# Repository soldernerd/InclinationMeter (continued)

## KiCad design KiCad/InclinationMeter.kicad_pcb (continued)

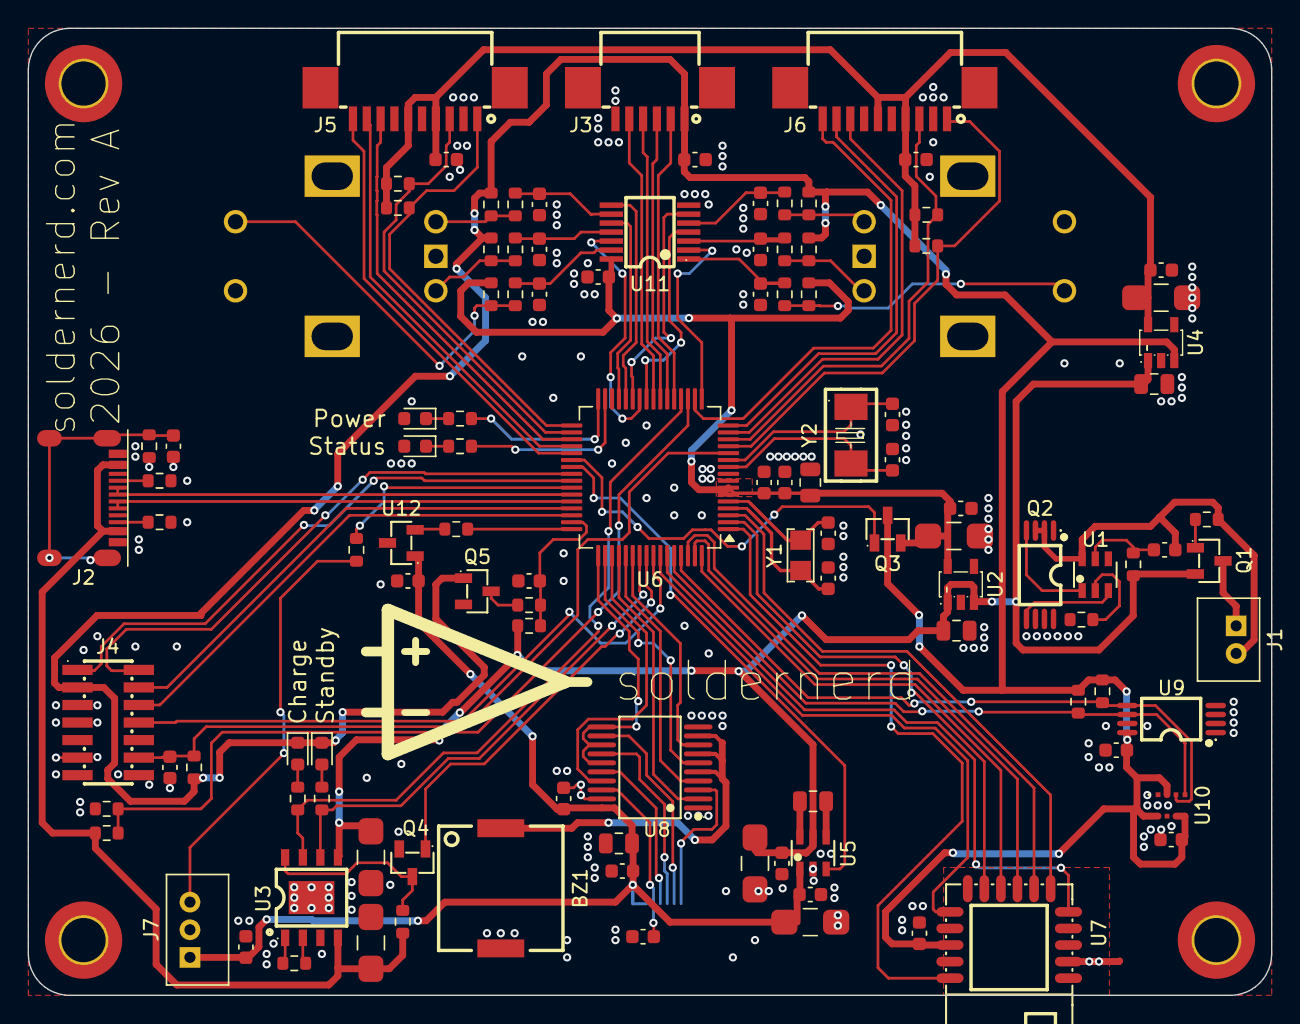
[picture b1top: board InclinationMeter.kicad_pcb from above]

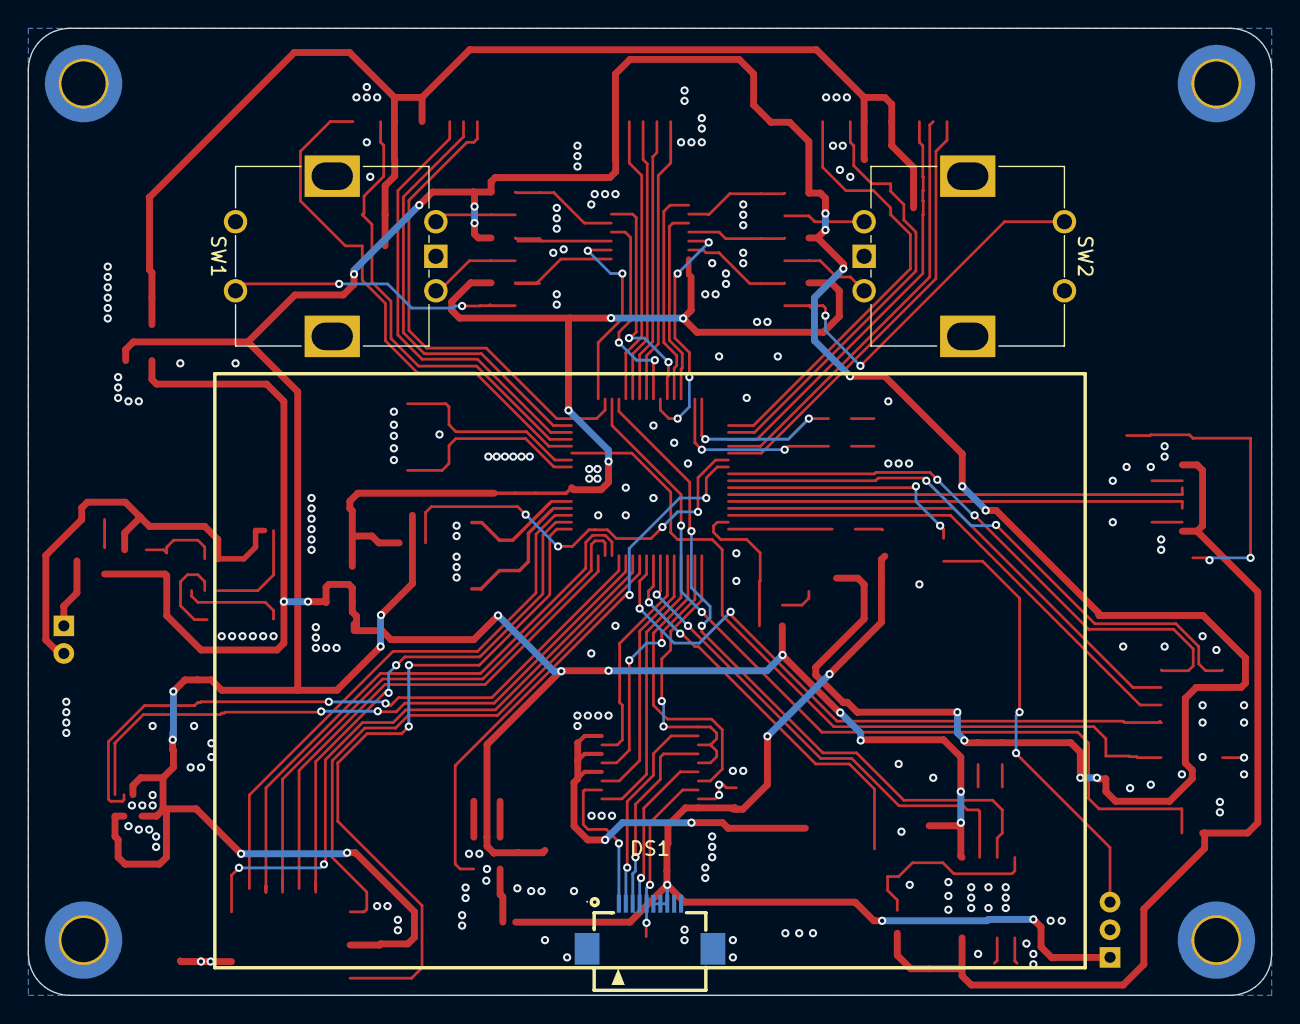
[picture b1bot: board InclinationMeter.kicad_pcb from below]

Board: 4 copper layers, 90.0 x 70.0 mm, 118 parts (3 on the bottom side), 105 nets.

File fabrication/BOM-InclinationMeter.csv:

"Comment","Designator","Footprint","LCSC Part #"
"CPT-9019A-SMT-TR","BZ1","sldrnrd:CPT-9019A","C20181991"
"1u","C1,C6,C16","sldrnrd:C_0805","C28323"
"100n","C2,C3,C8,C11,C12,C13,C17,C18,C23,C26,C27,C28,C30,C32,C34,C35,C36,C37,C38,C39,C40,C41,C42,C43","sldrnrd:C_0603","C14663"
"10u","C4,C5,C7,C9,C10,C14","sldrnrd:C_1206","C70462"
"2u2","C15,C29","sldrnrd:C_0805","C126589"
"15p","C19,C20","sldrnrd:C_0603","C1644"
"33p","C21,C22","sldrnrd:C_0603","C1663"
"10n","C24,C25,C31,C33","sldrnrd:C_0603","C57112"
"LED_Red_0603","D1","sldrnrd:LED_0603","C2286"
"LED_Green_0603","D2,D3","sldrnrd:LED_0603","C72043"
"LED_Yellow_0603","D4","sldrnrd:LED_0603","C2287"
"LS027B7DH01","DS1","sldrnrd:Display_LS027B7DH01","C17492463"
"JST_PH_2.0mm_1x02","J1","sldrnrd:JST_PH_2.0mm_1x02","C131337"
"USB_C","J2","sldrnrd:USB_C","C165948"
"Header_FFC_1.0mm_06","J3","sldrnrd:Header_FFC_1.0mm_06","C72727"
"Header_50mil_2x07","J4","sldrnrd:Header_50mil_2x07","C5563894"
"Header_FFC_1.0mm_10","J5,J6","sldrnrd:Header_FFC_1.0mm_10","C52162"
"JST_PH_2.0mm_1x03","J7","sldrnrd:JST_PH_2.0mm_1x03","C131339"
"DMG2305UX-13","Q1,Q3","sldrnrd:SOT-23-3","C144153"
"FS8205A","Q2","sldrnrd:TSSOP-8","C14212"
"AO3400A","Q4,Q5","sldrnrd:SOT-23-3","C20917"
"100k","R1,R8,R28,R31","sldrnrd:R_0603","C25803"
"2k","R2,R26,R37","sldrnrd:R_0603","C22975"
"1k","R3,R6,R7,R10,R11","sldrnrd:R_0603","C21190"
"R_0603","R4","sldrnrd:R_0603",""
"33k","R5,R9,R12,R13,R14,R15,R16,R17,R20,R21,R22,R23,R24,R25,R34","sldrnrd:R_0603","C4216"
"5k1","R18,R19,R27,R29,R32,R33,R35,R36","sldrnrd:R_0603","C23186"
"68k","R30","sldrnrd:R_0603","C23231"
"PEC11R-4215F-S0024","SW1,SW2","sldrnrd:RotaryEncoder_PEC11R","C143790"
"DW01A","U1","sldrnrd:SOT-23-6","C85680"
"LP5907MFX-3.3/NOPB","U2,U4","sldrnrd:SOT-23-5","C80670"
"TP4056","U3","sldrnrd:ESOP-8","C382139"
"SD6210A","U5","sldrnrd:SOT-23-6","C250809"
"STM32G0B1RET6","U6","sldrnrd:LQFP-64","C2829307"
"RN4871-I/RM128","U7","sldrnrd:RN4871","C633941"
"SN74AHCT244DBR","U8","sldrnrd:SSOP-20","C2868870"
"24LC256-I/ST","U9","sldrnrd:TSSOP-8","C87823"
"BME280","U10","sldrnrd:LGA-8_2.5x2.5mm_P0.65mm","C92489"
"SN74HC14PWR","U11","sldrnrd:TSSOP-14","C6821"
"LM35","U12","sldrnrd:SOT-23-3","C9900081740"
"Q13FC1350000400","Y1","sldrnrd:CRYSTAL-3215","C32346"
"X50328MSB2GI","Y2","sldrnrd:CRYSTAL-3225","C115962"

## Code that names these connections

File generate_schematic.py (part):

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    # (name, pin_number, electrical_type)
    # Left side: pins 1–16 (top to bottom)
    left_pins = [
        ("PC11",    "1",  "bidirectional"),
        ("PC12",    "2",  "bidirectional"),
        ("PC13",    "3",  "bidirectional"),
        ("PC14",    "4",  "bidirectional"),
        ("PC15",    "5",  "bidirectional"),
        ("VBAT",    "6",  "power_in"),
        ("VREF+",   "7",  "power_in"),
        ("VDD",     "8",  "power_in"),
        ("VSS",     "9",  "power_in"),
        ("PF0",     "10", "input"),
        ("PF1",     "11", "output"),
        ("~{NRST}", "12", "input"),
        ("PC0",     "13", "bidirectional"),
        ("PC1",     "14", "bidirectional"),
        ("PC2",     "15", "bidirectional"),
        ("PC3",     "16", "bidirectional"),
    ]
    # Bottom side: pins 17–32 (left to right)
    bot_pins = [
        ("PA0",     "17", "bidirectional"),
        ("PA1",     "18", "bidirectional"),
        ("PA2",     "19", "bidirectional"),
        ("PA3",     "20", "bidirectional"),
        ("PA4",     "21", "bidirectional"),
        ("PA5",     "22", "bidirectional"),
        ("PA6",     "23", "bidirectional"),
        ("PA7",     "24", "bidirectional"),
        ("PC4",     "25", "bidirectional"),
        ("PC5",     "26", "bidirectional"),
        ("PB0",     "27", "bidirectional"),
        ("PB1",     "28", "bidirectional"),
        ("PB2",     "29", "bidirectional"),
        ("PB10",    "30", "bidirectional"),
        ("PB11",    "31", "bidirectional"),
        ("PB12",    "32", "bidirectional"),
    ]
    # Right side: pins 33–48 (bottom to top)
    right_pins = [
        ("PB13",    "33", "bidirectional"),
        ("PB14",    "34", "bidirectional"),
        ("PB15",    "35", "bidirectional"),
        ("PA8",     "36", "bidirectional"),
        ("PA9",     "37", "bidirectional"),
        ("PC6",     "38", "bidirectional"),
        ("PC7",     "39", "bidirectional"),
        ("PD8",     "40", "bidirectional"),
        ("PD9",     "41", "bidirectional"),
        ("PA10",    "42", "bidirectional"),
        ("PA11",    "43", "bidirectional"),
        ("PA12",    "44", "bidirectional"),
        ("PA13",    "45", "bidirectional"),
        ("PA14",    "46", "input"),
        ("PA15",    "47", "bidirectional"),
        ("PC8",     "48", "bidirectional"),
    ]
    # Top side: pins 49–64 (right to left)
    top_pins = [
        ("PC9",     "49", "bidirectional"),
        ("PD0",     "50", "bidirectional"),
        ("PD1",     "51", "bidirectional"),
        ("PD2",     "52", "bidirectional"),
        ("PD3",     "53", "bidirectional"),
        ("PD4",     "54", "bidirectional"),
        ("PD5",     "55", "bidirectional"),
        ("PD6",     "56", "bidirectional"),
        ("PB3",     "57", "bidirectional"),
        ("PB4",     "58", "bidirectional"),
        ("PB5",     "59", "bidirectional"),
        ("PB6",     "60", "bidirectional"),
        ("PB7",     "61", "bidirectional"),
        ("PB8",     "62", "bidirectional"),
        ("PB9",     "63", "bidirectional"),
        ("PC10",    "64", "bidirectional"),
    ]

    # Geometry: 16 pins per side, 2.54 mm spacing
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    # Pin connections per Netlist.md
    # Left side (pins 1-10): inputs from MCU (3.3V signals)
    p1 = pin("SN74AHCT244", "1", ax, ay)   # 1OE -> GND
    p2 = pin("SN74AHCT244", "2", ax, ay)   # 1A1 <- DISP_SCK
    p4 = pin("SN74AHCT244", "4", ax, ay)   # 1A2 <- DISP_MOSI
    p6 = pin("SN74AHCT244", "6", ax, ay)   # 1A3 <- DISP_CS
    p8 = pin("SN74AHCT244", "8", ax, ay)   # 1A4 <- DISP_VCOM
    p10 = pin("SN74AHCT244", "10", ax, ay)  # GND

    gnd(el, p1[0], p1[1])   # 1OE always enabled
    gnd(el, p10[0], p10[1])  # GND pin

    glabel_left(el, p2[0], p2[1], "DISP_SCK", "input")
    glabel_left(el, p4[0], p4[1], "DISP_MOSI", "input")
    glabel_left(el, p6[0], p6[1], "DISP_CS", "input")
    glabel_left(el, p8[0], p8[1], "DISP_VCOM", "input")

    # Spare inputs (3, 5, 7) - tie unused to GND (pin 9 is 2OE, handled below)
    for pn in ["3", "5", "7"]:
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        gnd(el, pp[0], pp[1])

    # Right side (pins 11-20): outputs (5V signals)
    p11 = pin("SN74AHCT244", "11", ax, ay)  # 2A1 <- DISP_ON
    p18 = pin("SN74AHCT244", "18", ax, ay)  # 1Y1 -> DISP_SCK_5V
    p16 = pin("SN74AHCT244", "16", ax, ay)  # 1Y2 -> DISP_MOSI_5V
    p14 = pin("SN74AHCT244", "14", ax, ay)  # 1Y3 -> DISP_CS_5V
    p12 = pin("SN74AHCT244", "12", ax, ay)  # 1Y4 -> DISP_VCOM_5V
    p9_r = pin("SN74AHCT244", "9", ax, ay)  # 2Y1 -> DISP_ON_5V
    p19 = pin("SN74AHCT244", "19", ax, ay)  # 2OE -> GND
    p20 = pin("SN74AHCT244", "20", ax, ay)  # VCC -> +5V

    glabel_left(el, p11[0], p11[1], "DISP_ON", "input")

    pwr5v(el, p20[0], p20[1])
    gnd(el, p19[0], p19[1])  # 2OE always enabled

    label_right(el, p18[0], p18[1], "DISP_SCK_5V")
    label_right(el, p16[0], p16[1], "DISP_MOSI_5V")
    label_right(el, p14[0], p14[1], "DISP_CS_5V")
    label_right(el, p12[0], p12[1], "DISP_VCOM_5V")
    label_right(el, p9_r[0], p9_r[1], "DISP_ON_5V")

    # Spare outputs: pins 13, 15, 17 -> tie inputs to GND already done above
    for pn in ["13", "15", "17"]:
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
    # Display connector pinout per Netlist.md
    jp = lambda n: pin("FH12_10S", str(n), jx, jy)
    label_left(el, jp(1)[0], jp(1)[1], "DISP_SCK_5V")
    label_left(el, jp(2)[0], jp(2)[1], "DISP_MOSI_5V")
    label_left(el, jp(3)[0], jp(3)[1], "DISP_CS_5V")
    label_left(el, jp(4)[0], jp(4)[1], "DISP_VCOM_5V")
    label_left(el, jp(5)[0], jp(5)[1], "DISP_ON_5V")
    pwr5v(el, jp(6)[0], jp(6)[1])   # EXTMODE tied to +5V
    pwr5v(el, jp(7)[0], jp(7)[1])   # VDD
    gnd(el, jp(8)[0], jp(8)[1])     # VSS
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
    # Right pins
    el.append(sexp_no_connect(rp(9)[0], rp(9)[1]))    # P3_6
    glabel_right(el, rp(10)[0], rp(10)[1], "BLE_RST", "input")  # RST_N
    glabel_right(el, rp(11)[0], rp(11)[1], "BLE_STATUS", "output")  # P0_0 status
    el.append(sexp_no_connect(rp(12)[0], rp(12)[1]))  # P0_2
    gnd(el, rp(13)[0], rp(13)[1])                      # GND
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    el.append(sexp_text("22R series on D+/D-", 60, 102, 1.27))

    # VBUS sense
    el.append(sexp_global_label("VBUS_SENSE", 50, 115, 0, "output"))
    el.append(sexp_text("Optional VBUS detect", 60, 122, 1.27))

    # ── SWD Debug Header J3 ──
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    gnd(el, fp("03")[0], fp("03")[1])                            # Pin 3: GND
    glabel_right(el, fp("04")[0], fp("04")[1], "SWCLK", "output")       # Pin 4: SWCLK (via 100R)
    gnd(el, fp("05")[0], fp("05")[1])                            # Pin 5: GND
    el.append(sexp_no_connect(fp("06")[0], fp("06")[1]))        # Pin 6: SWO (NC)
    el.append(sexp_no_connect(fp("07")[0], fp("07")[1]))        # Pin 7: NC
    el.append(sexp_no_connect(fp("08")[0], fp("08")[1]))        # Pin 8: NC
    gnd(el, fp("09")[0], fp("09")[1])                            # Pin 9: GND
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    gnd(el, fp("14")[0], fp("14")[1])                            # Pin 14: GND

    el.append(sexp_text("100R series on SWDIO/SWCLK", 177, 120, 1.27))
    el.append(sexp_text("10k BOOT0 pull-down on PA14/SWCLK", 177, 127, 1.27))
    el.append(sexp_text("10k pull-up + 100nF on NRST", 177, 134, 1.27))

    # ── FFC Connectors (J5, J6, J7) ──
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    place_resistor(el, ld1x, ld1y, next_ref("R"), "330R")
    r1t = pin("R", "1", ld1x, ld1y)
    r1b = pin("R", "2", ld1x, ld1y)
    glabel_left(el, r1t[0], r1t[1], "LED_PWR", "input", 10)
    el.append(sexp_symbol_instance("inline:LED", next_ref("D"), "Green",
                                   "LED_SMD:LED_0603_1608Metric", ld1x, ld1y + 10))
    la = pin("LED", "1", ld1x, ld1y + 10)
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
    bp1 = pin("CPT_9019A", "1", bx, by)
    bp2 = pin("CPT_9019A", "2", bx, by)
    glabel_left(el, bp1[0], bp1[1], "BUZZER", "input")
    gnd(el, bp2[0], bp2[1])
    el.append(sexp_text("PWM 4kHz from TIM1_CH2 (PB3)", 217, 152, 1.27))

    # ── EEPROM ──
    el.append(sexp_rect(27, 170, 195, 270))
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    # Pin 3 (GND) → GND
    lm_gnd = pin("LM35", "3", lmx, lmy)
    gnd(el, lm_gnd[0], lm_gnd[1])
    # Pin 2 (VOUT) → R_TEMP 100R → C_TEMP 10nF → TEMP_SENSE global label
    lm_out = pin("LM35", "2", lmx, lmy)
    # Series resistor R_TEMP
    rt_ref = next_ref("R")
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    ct_ref = next_ref("C")
    ctx, cty = rtx + 7, rty + 5
    place_bypass_cap(el, ctx, cty, ct_ref, "10nF")
    # Wire from R bottom to junction, then to cap and to TEMP_SENSE label
    jx, jy = rt_bot[0], rt_bot[1]
    el.append(sexp_wire(jx, jy, ctx, jy))
    el.append(sexp_junction(ctx, jy))
    glabel_right(el, jx, jy, "TEMP_SENSE", "output")

    content = "\n".join(el)
    return wrap_schematic(content, title="User Interface & Peripherals",
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
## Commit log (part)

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2026-05-02 Schematics edited manually
2026-05-10 Schematic finalized
2026-05-14 Basic board layout changed. MCU pinout changed accordingly
2026-05-14 Encoder fixed, main parts and dimensions locked
2026-05-15 Board largely routed, except power and gnd
2026-05-22 Environmental sensor added, mostly routed.
2026-05-23 Routed with no errors, silkscreen done
2026-05-23 External temperature sensor added
2026-05-27 JST headers fixed, no more errors, fully routed
2026-05-31 Capacitors changed to specific symbols, board layout not yet complete
2026-06-12 Board layout finalized, first gerbers generated
2026-06-12 crystal capacitors changed to correct values
2026-06-12 Symbols and board updated to match library
2026-06-12 Remaining resistors and capacitors replaced by specific value components
2026-06-12 R30 fixed as well
2026-06-12 R4 changed to 2k
